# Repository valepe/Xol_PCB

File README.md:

# Xol PCB

This is a PCB made for Armchair Engineering's [Xol Toolhead](https://github.com/Armchair-Engineering/Xol-Toolhead), featuring:
* One hotend cooling fan JST-XH connectors with diode for tach signal
* Two part cooling  fan JST-XH connectors
* One heater Micro-Fit connector
* One thermistor Micro-Fit connector
* One Neopixel JST-XH connector with resistor for the data line
* Two auxiliary JST-XH connectors
* One extruder motor connector
* Selectable fan voltage (5V, Alt, 24V)
* Integrated mount for carriage screw

I customized the Xol Toolhead board by [ruiqimao](https://github.com/ruiqimao/VoronStuff/tree/main/Xol_PCB) to suite my needs:
* A three pins connector for the hotend fan with tach signal and its diode
* A resistor for the RGB data line to avoid signal noise for the cable length
* Three AUX pins for X-endstop and the two filament sensors

**ATTENTION!** This pcb isn't pin compatible with ruiqimao one starting from the main connector (from 16 to 18 pins). Even the thermistor and hotend connectors are swapped. Check carefully the pinout!

## BOM

In addition to the PCB, the following things are needed:

| Part | Quantity | Link |
|:-:|:-:|:-:|
| Molex Micro-Fit 3.0 430451800 | 1 | [DigiKey](https://www.digikey.com/en/products/detail/molex/0430451800/531425) |
| Molex Micro-Fit 3.0 430650200 | 2 | [DigiKey](https://www.digikey.com/en/products/detail/molex/0436500200/268989) |
| JST B2B-XH-A | 2 | [DigiKey](https://www.digikey.com/en/products/detail/jst-sales-america-inc./B2B-XH-A(LF)(SN)/1651045) |
| JST B3B-XH-A | 4 | [DigiKey](https://www.digikey.com/en/products/detail/jst-sales-america-inc./B3B-XH-A/1651046) |
| JST B4B-XH-A | 1 | [DigiKey](https://www.digikey.com/en/products/detail/jst-sales-america-inc./B4B-XH-A(LF)(SN)/1651047) |
| BAT85 diode | 1 | [DigiKey](https://www.digikey.com/en/products/detail/nexperia-usa-inc/BAT85-133/1232135) |
| 470 Ohm resistor | 1 | [DigiKey](https://www.digikey.com/en/products/detail/stackpole-electronics-inc/CF14JT470R/1741440) |

## Pinout

From the point of view looking directly at the **wiring harness connector**:

| Pin | Usage | Pin | Usage |
|:-:|:-:|:-:|:-:|
| 1 | Neopixel | 10 | Auxiliary 2 |
| 2 | Part cooling fan ground | 11 | Auxiliary 3 |
| 3 | Hotend fan ground | 12 | Alt voltage |
| 4 | Thermistor ground | 13 | Thermistor |
| 5 | Motor A1 | 14 | Motor B1 |
| 6 | Motor A2 | 15 | Motor B2 |
| 7 | Ground | 16 | Hotend fan tach |
| 8 | 5V | 17 | Auxiliary 1 |
| 9 | Hotend voltage | 18 | Hotend ground |

## Selectable fan voltage

There are two sets of solder jumpers, one for each type of fan, that should be bridged to select the fan voltage.

## Extruder compatibility
The PCB and strain relief are designed with only the [Sherpa Mini](https://github.com/Annex-Engineering/Sherpa_Mini-Extruder) in mind. **Usage with other extruders may require the motor connector to be swapped to the back side.**

## Credits

Credits to the great work of XOL Toolhead board by [ruiqimao](https://github.com/ruiqimao/VoronStuff/tree/main/Xol_PCB).

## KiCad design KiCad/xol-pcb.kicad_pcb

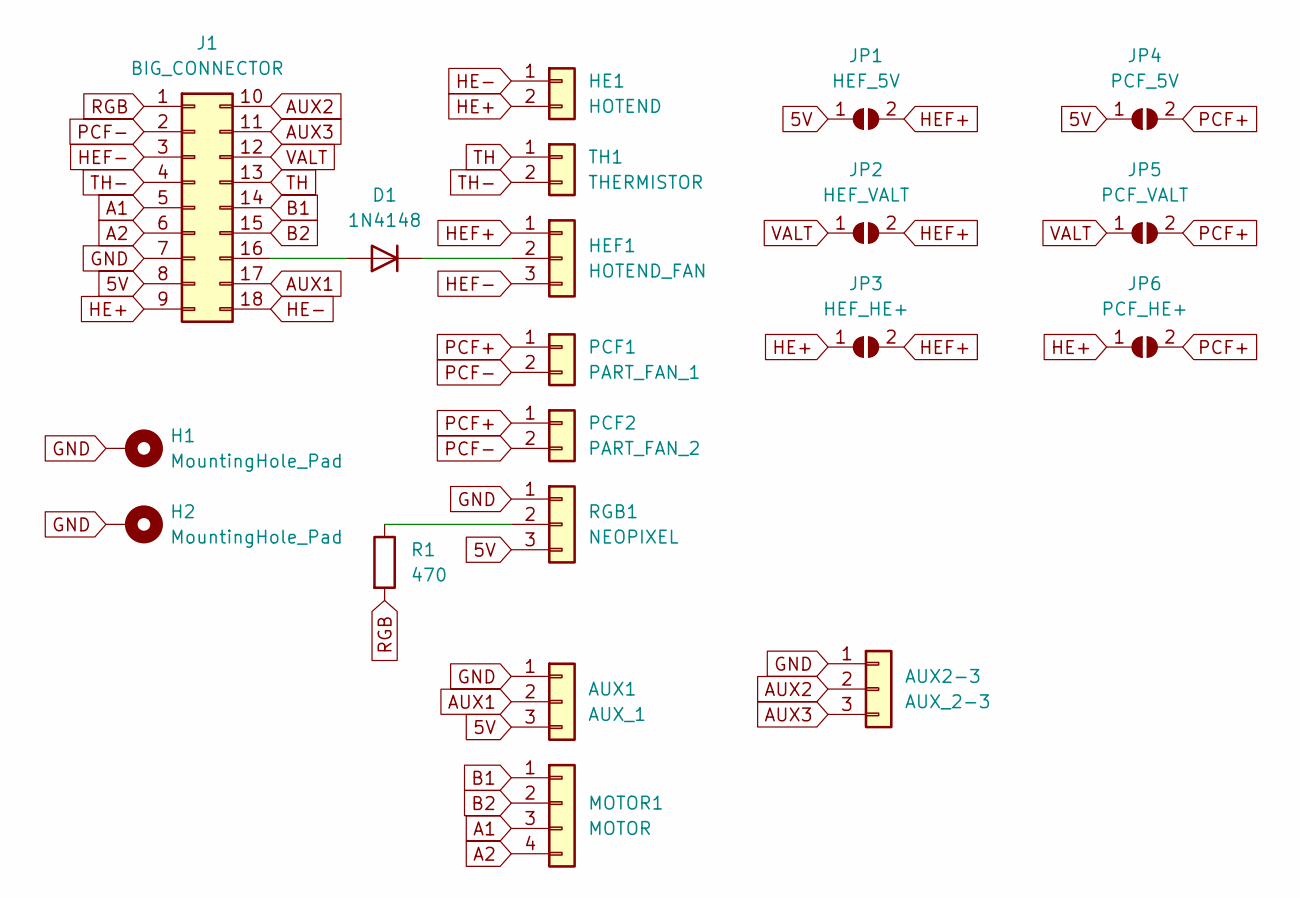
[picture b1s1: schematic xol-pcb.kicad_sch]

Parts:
AUX1: AUX_1; JST_XH_B3B-XH-A_1x03_P2.50mm_Vertical
AUX2-3: AUX_2-3; JST_XH_B3B-XH-A_1x03_P2.50mm_Vertical
D1: 1N4148; D_DO-35_SOD27_P7.62mm_Horizontal
H1, H2: MountingHole_Pad; MountingHole_3.2mm_M3_Pad
HE1: HOTEND; Molex_Micro-Fit_3.0_43650-0200_1x02_P3.00mm_Horizontal
HEF1: HOTEND_FAN; JST_XH_B3B-XH-A_1x03_P2.50mm_Vertical
J1: BIG_CONNECTOR; Molex_Micro-Fit_3.0_43045-1800_2x09_P3.00mm_Horizontal
JP1: HEF_5V; SolderJumper-2_P1.3mm_Open_TrianglePad1.0x1.5mm
JP2: HEF_VALT; SolderJumper-2_P1.3mm_Open_TrianglePad1.0x1.5mm
JP3: HEF_HE+; SolderJumper-2_P1.3mm_Open_TrianglePad1.0x1.5mm
JP4: PCF_5V; SolderJumper-2_P1.3mm_Open_TrianglePad1.0x1.5mm
JP5: PCF_VALT; SolderJumper-2_P1.3mm_Open_TrianglePad1.0x1.5mm
JP6: PCF_HE+; SolderJumper-2_P1.3mm_Open_TrianglePad1.0x1.5mm
MOTOR1: MOTOR; JST_XH_B4B-XH-A_1x04_P2.50mm_Vertical
PCF1: PART_FAN_1; JST_XH_B2B-XH-A_1x02_P2.50mm_Vertical
PCF2: PART_FAN_2; JST_XH_B2B-XH-A_1x02_P2.50mm_Vertical
R1: 470; R_Axial_DIN0207_L6.3mm_D2.5mm_P7.62mm_Horizontal
RGB1: NEOPIXEL; JST_XH_B3B-XH-A_1x03_P2.50mm_Vertical
TH1: THERMISTOR; Molex_Micro-Fit_3.0_43650-0200_1x02_P3.00mm_Horizontal

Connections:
5V: AUX1.3, J1.8, JP1.1 (A), JP4.1 (A), RGB1.3
A1: J1.5, MOTOR1.3
A2: J1.6, MOTOR1.4
AUX1: AUX1.2, J1.17
AUX2: AUX2-3.2, J1.10
AUX3: AUX2-3.3, J1.11
B1: J1.14, MOTOR1.1
B2: J1.15, MOTOR1.2
GND: AUX1.1, AUX2-3.1, H1.1, H2.1, J1.7, RGB1.1
HE+: HE1.2, J1.9, JP3.1 (A), JP6.1 (A)
HE-: HE1.1, J1.18
HEF+: HEF1.1, JP1.2 (B), JP2.2 (B), JP3.2 (B)
HEF-: HEF1.3, J1.3
unnamed: D1.2 (A), J1.16
unnamed: D1.1 (K), HEF1.2
unnamed: R1.1, RGB1.2
PCF+: JP4.2 (B), JP5.2 (B), JP6.2 (B), PCF1.1, PCF2.1
PCF-: J1.2, PCF1.2, PCF2.2
RGB: J1.1, R1.2
TH: J1.13, TH1.1
TH-: J1.4, TH1.2
VALT: J1.12, JP2.1 (A), JP5.1 (A)

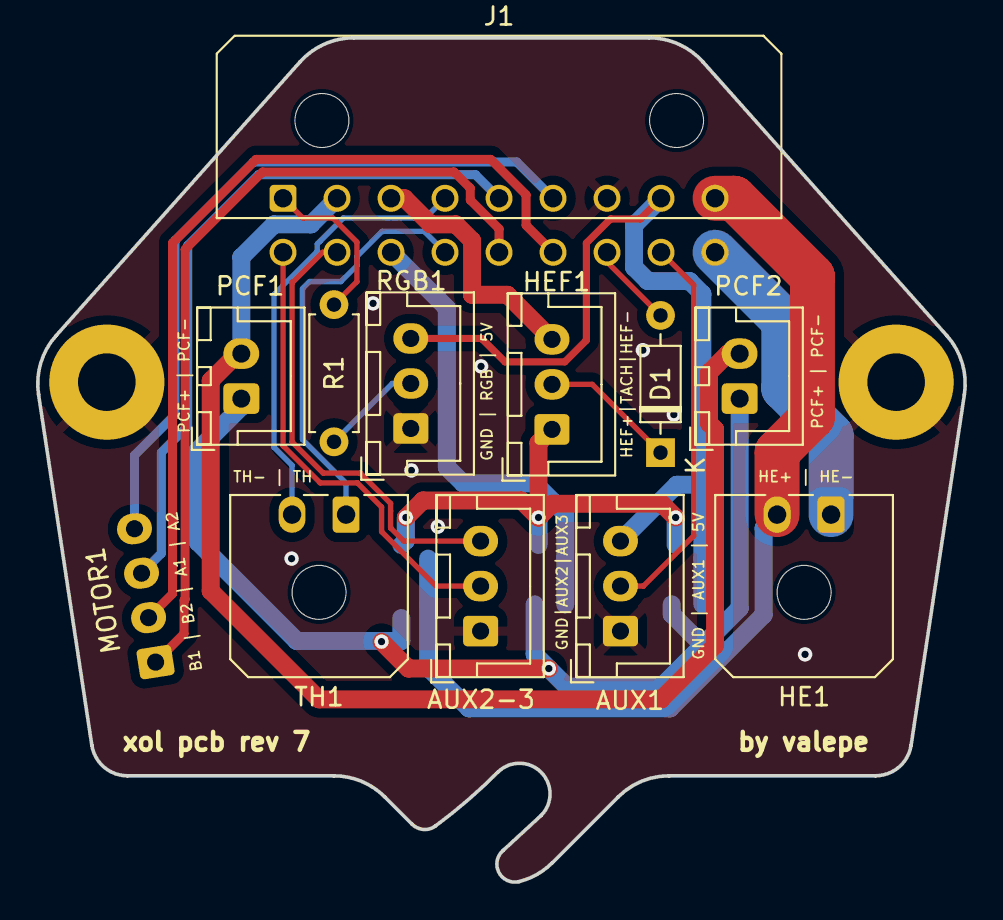
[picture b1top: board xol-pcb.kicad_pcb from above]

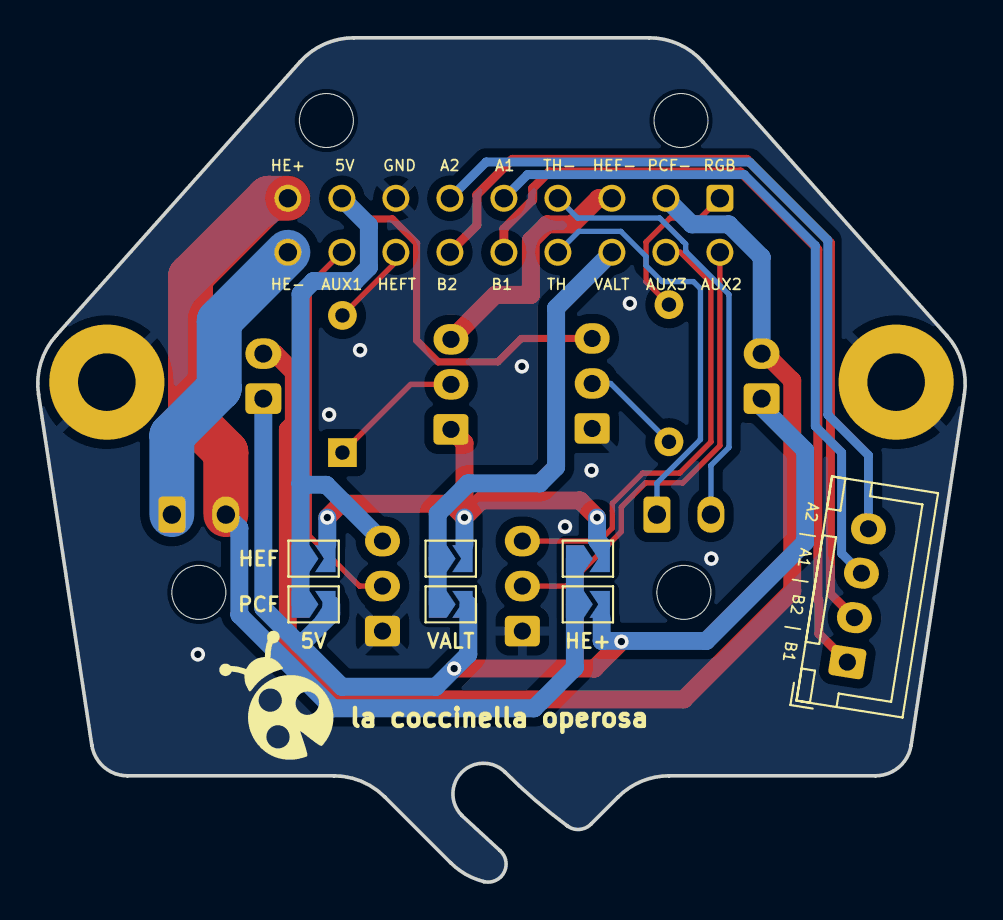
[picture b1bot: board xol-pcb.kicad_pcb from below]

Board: 2 copper layers, 51.5 x 46.9 mm, 20 parts (7 on the bottom side), 22 nets.

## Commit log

2025-01-30 Create pi
